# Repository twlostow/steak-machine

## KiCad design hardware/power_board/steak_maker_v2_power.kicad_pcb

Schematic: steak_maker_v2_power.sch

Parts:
B1, B2, B3, B4: NON-PLATED_HOLE3.0; MTG300; Part Number NON-PLATED_HOLE3.0
C1: CAER_470UF_10V_20%_500-1050X1150_LESR0R015; CAPPR500-1050X1150; Voltage 10V; Tolerance ±20%; Part Number CAER_470UF_10V_20%_500-1050X1150_LESR0R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
C2, C4: CCR_100NF_50V_10%_KEMET_C322C104K5R5TA; CAPRR508-318X508X660; Voltage 50VDC; Tolerance ±10%; Part Number CCR_100NF_50V_10%_KEMET_C322C104K5R5TA
C3: CAER_100UF_16V_20%_CHEMI-CON_APSA160ELL101MFA5G; CAPPR250-680X1080; Voltage 16V; Tolerance ±20%; Part Number CAER_100UF_16V_20%_CHEMI-CON_APSA160ELL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
D1, D2, D3, D4: 1N4007; DO-41; Voltage 1000V; Part Number 1N4007
IC1: LM7805CT_h; TO-220-H; Part Number LM7805CT_h
IC2, IC3: MOC3041M; DIP6-300
J1, J2, J4, J5, J9, J10, J11, J12: TYCO_62409-1; Part Number TYCO_62409-1
J8: MAIN
Q1, Q2: BT138-800; TO-220-v
R1, R2, R3, R4: RMF_150R_1%_0.125W_100PPM_1016-360X210; RES1016-360X210; Voltage ~~; Tolerance ±1%; Part Number RMF_150R_1%_0.125W_100PPM_1016-360X210
T1: Transformer_1P_1S; XFMR_BLOCK_10_1_6

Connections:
+5V: C3.1, C4.1, IC1.3, J8.1
/AC_L: J4.1, J9.1, J11.1, T1.1
/AC_N: J5.1, Q1.2 (A2), Q2.2 (A2), R3.2, R4.2, T1.2
/TRIAC1: J8.2, R1.1
/TRIAC2: J8.4, R2.1
GND: C1.2, C2.2, C3.2, C4.2, D3.2, D4.2, IC1.2, IC1.4, IC2.2, IC3.2, J1.1, J2.1, J8.3
unnamed: C1.1, C2.1, D1.1, D2.1, IC1.1
unnamed: D1.2, D3.1, T1.4
unnamed: D2.2, D4.1, T1.3
unnamed: IC2.1, R1.2
unnamed: IC2.4, Q1.3 (G)
unnamed: IC2.6, R3.1
unnamed: IC3.1, R2.2
unnamed: IC3.4, Q2.3 (G)
unnamed: IC3.6, R4.1
unnamed: J10.1, Q1.1 (A1)
unnamed: J12.1, Q2.1 (A1)

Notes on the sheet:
AC Input
Heater 1
Heater 2

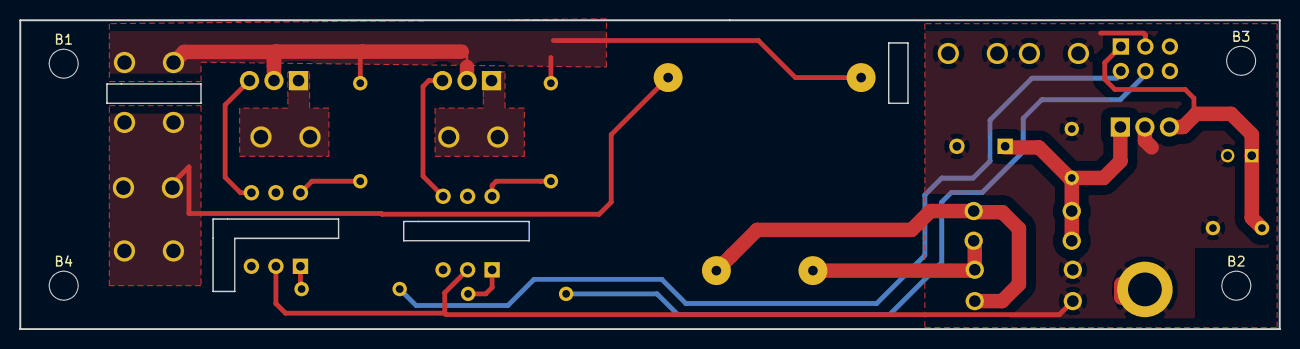
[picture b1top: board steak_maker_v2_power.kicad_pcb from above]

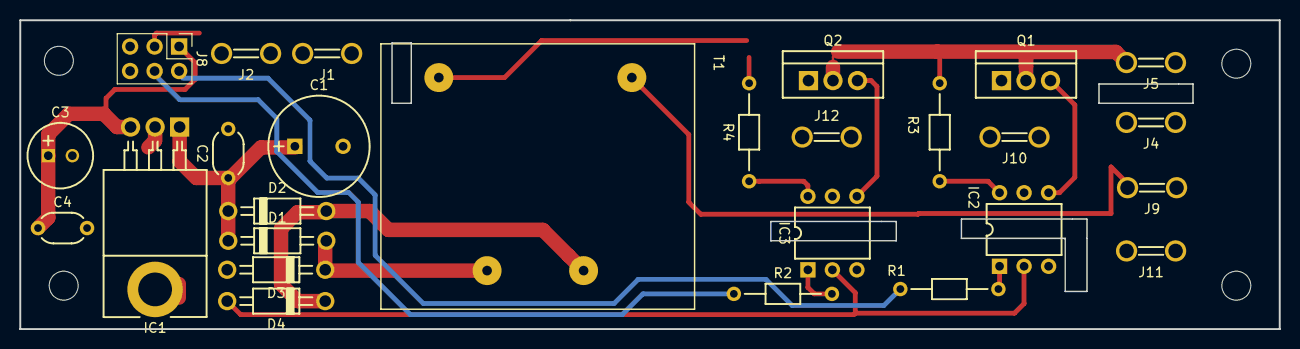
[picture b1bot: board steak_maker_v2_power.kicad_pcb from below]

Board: 2 copper layers, 130.5 x 32.0 mm, 31 parts (27 on the bottom side), 17 nets.

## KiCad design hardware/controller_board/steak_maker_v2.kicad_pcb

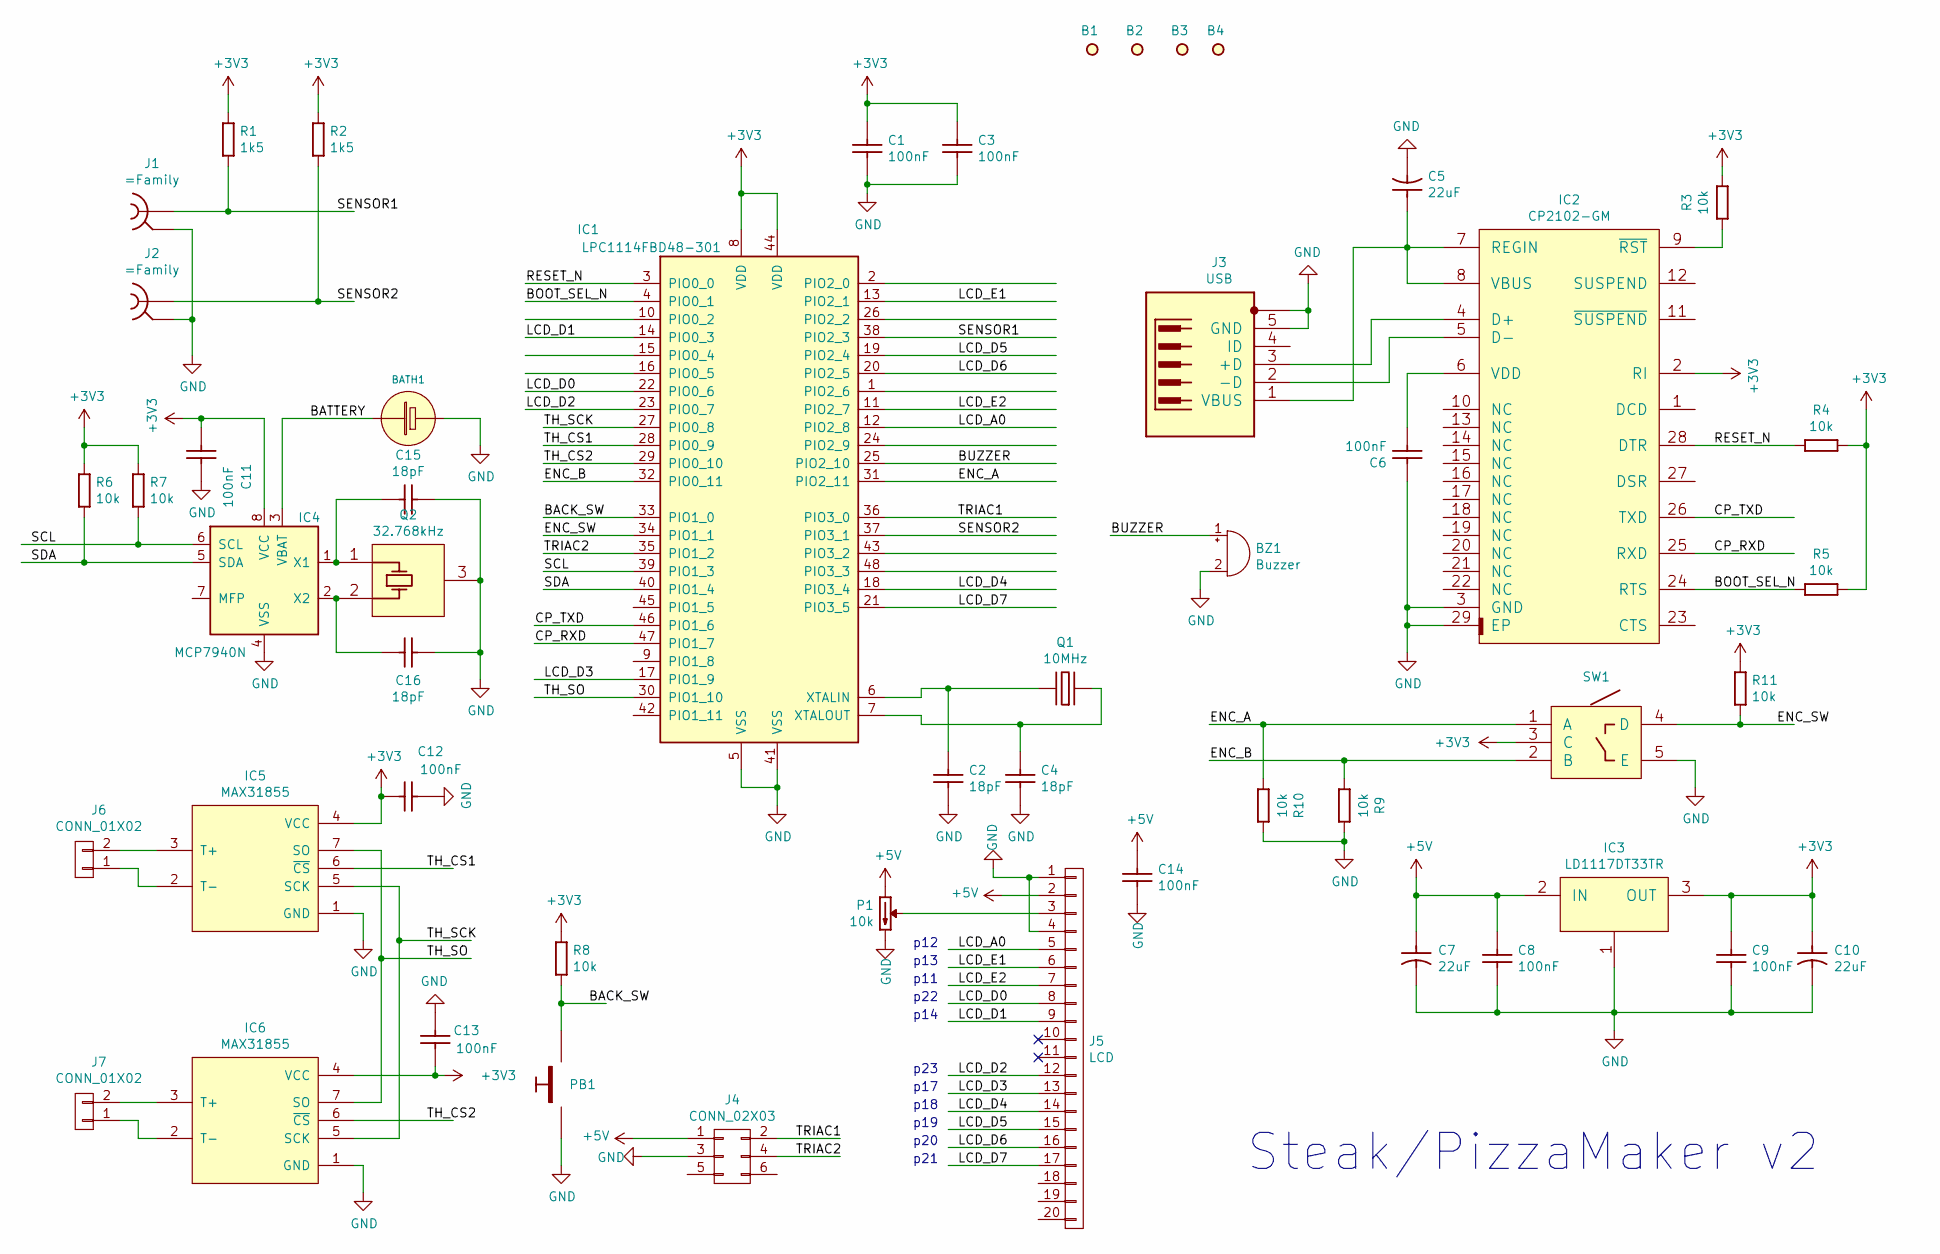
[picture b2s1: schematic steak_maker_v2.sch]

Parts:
B1, B2, B3, B4: PLATED_HOLE3.0_PAD6.0; MTG300_600; Part Number PLATED_HOLE3.0_PAD6.0
BATH1: BATH_KEYSTONE_103; Part Number BATH_KEYSTONE_103
BZ1: Buzzer; MagneticBuzzer_ProSignal_ABT-410-RC
C1, C3, C6, C8, C9, C11, C12, C13, C14: CC0603_100NF_100V_10%_X7R; CAPC1608X90N; Voltage 100V; Tolerance ±10%; Part Number CC0603_100NF_100V_10%_X7R
C2, C4, C15, C16: CC0603_18PF_50V_5%_NP0; CAPC1608X87N; Voltage 50V; Tolerance ±5%; Part Number CC0603_18PF_50V_5%_NP0
C5, C7, C10: CTE3528-21_22UF_10V_10%_LESR0700; CAPMP3528X210N; Voltage 10V; Tolerance ±10%; Part Number CTE3528-21_22UF_10V_10%_LESR0700
IC1: LPC1114FBD48-301; LQFP-48_7x7mm_Pitch0.5mm
IC2: CP2102-GM; QFN50P500X500X100-29N-S335; Part Number CP2102-GM
IC3: LD1117DT33TR; TO228P972X240-3N-R540X510; Part Number LD1117DT33TR
IC4: MCP7940N; SOIC127P600X175-8N
IC5, IC6: MAX31855; SOIC127P600X175-8N
J1, J2: LEMO_EPA.00.250.NTN; Part Number LEMO_EPA.00.250.NTN
J3: MOLEX_500075-1517; Part Number MOLEX_500075-1517
J4: CONN_02X03; COMATEL_389.0358.1.06.400
J5: LCD; COMATEL_385.0334.1.20.400
J6, J7: CONN_01X02; TerminalBlock_Pheonix_PT-3.5mm_2pol
P1: TRIM_12T_10K_BOURNS_3266W-1-103LF; TRIM_BOURNS_3266W; Tolerance ±10%; Part Number TRIM_12T_10K_BOURNS_3266W-1-103LF
PB1: PB_MULTIMEC_3ETL9-11.0; Part Number PB_MULTIMEC_3ETL9-11.0
Q1: XTAL_10MHZ_IQD_LFXTAL003166; XTAL1160X490X430; Part Number XTAL_10MHZ_IQD_LFXTAL003166
Q2: XTAL_32.768_KHZ_MICRO-CRYSTAL_MS3V-T1R; XTAL_MICRO-CRYSTAL_MS3V-T1R; Part Number XTAL_32.768_KHZ_MICRO-CRYSTAL_MS3V-T1R
R1, R2: R0603_1K5_1%_0.1W_100PPM; RESC1608X55N; Voltage ~~; Tolerance ±1%; Part Number R0603_1K5_1%_0.1W_100PPM
R3, R4, R5, R6, R7, R8, R9, R10, R11: R0603_10K_1%_0.1W_100PPM; RESC1608X55N; Voltage ~~; Tolerance ±1%; Part Number R0603_10K_1%_0.1W_100PPM
SW1: SW_ALPS_EC11B15242AE; SW_ALPS_EC11E; Part Number SW_ALPS_EC11B15242AE

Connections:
+3V3: C1.1, C3.1, C9.1, C10.1, C11.2, C12.2, C13.1, IC1.8 (VDD), IC1.44 (VDD), IC2.2 (RI), IC3.3 (OUT), IC4.8 (VCC), IC5.4 (VCC), IC6.4 (VCC), R1.1, R2.1, R3.2, R4.2, R5.2, R6.1, R7.1, R8.1, R11.1, SW1.3 (C)
+5V: C7.1, C8.1, C14.1, IC3.2 (IN), J4.1, J5.2, P1.1 (CCW)
/BACK_SW: IC1.33 (PIO1_0), PB1.3, PB1.4, R8.2
/BATTERY: BATH1.1 (PLUS), IC4.3 (VBAT)
/BOOT_SEL_N: IC1.4 (PIO0_1), IC2.24 (RTS), R5.1
/BUZZER: BZ1.1 (-), IC1.25 (PIO2_10)
/CP_RXD: IC1.47 (PIO1_7), IC2.25 (RXD)
/CP_TXD: IC1.46 (PIO1_6), IC2.26 (TXD)
/ENC_A: IC1.31 (PIO2_11), R10.2, SW1.1 (A)
/ENC_B: IC1.32 (PIO0_11), R9.2, SW1.2 (B)
/ENC_SW: IC1.34 (PIO1_1), R11.2, SW1.4 (D)
/LCD_A0: IC1.12 (PIO2_8), J5.5
/LCD_D0: IC1.22 (PIO0_6), J5.8
/LCD_D1: IC1.14 (PIO0_3), J5.9
/LCD_D2: IC1.23 (PIO0_7), J5.12
/LCD_D3: IC1.17 (PIO1_9), J5.13
/LCD_D4: IC1.18 (PIO3_4), J5.14
/LCD_D5: IC1.19 (PIO2_4), J5.15
/LCD_D6: IC1.20 (PIO2_5), J5.16
/LCD_D7: IC1.21 (PIO3_5), J5.17
/LCD_E1: IC1.13 (PIO2_1), J5.6
/LCD_E2: IC1.11 (PIO2_7), J5.7
/RESET_N: IC1.3 (PIO0_0), IC2.28 (DTR), R4.1
/SCL: IC1.39 (PIO1_3), IC4.6 (SCL), R7.2
/SDA: IC1.40 (PIO1_4), IC4.5 (SDA), R6.2
/SENSOR1: IC1.38 (PIO2_3), J1.1, R1.2
/SENSOR2: IC1.37 (PIO3_1), J2.1, R2.2
/TH_CS1: IC1.28 (PIO0_9), IC5.6 (~CS)
/TH_CS2: IC1.29 (PIO0_10), IC6.6 (~CS)
/TH_SCK: IC1.27 (PIO0_8), IC5.5 (SCK), IC6.5 (SCK)
/TH_SO: IC1.30 (PIO1_10), IC5.7 (SO), IC6.7 (SO)
/TRIAC1: IC1.36 (PIO3_0), J4.2
/TRIAC2: IC1.35 (PIO1_2), J4.4
GND: BATH1.2 (MINUS), BZ1.2 (+), C1.2, C2.2, C3.2, C4.2, C5.2, C6.1, C7.2, C8.2, C9.2, C10.2, C11.1, C12.1, C13.2, C14.2, C15.1, C16.1, IC1.5 (VSS), IC1.41 (VSS), IC2.3 (GND), IC2.29 (EP), IC3.1 (GND), IC4.4 (VSS), IC5.1 (GND), IC6.1 (GND), J1.2, J2.2, J3.5 (GND), J3.6 (SH), J4.3, J5.1, J5.4, P1.3 (CW), PB1.1, PB1.2, Q2.3 (GND), R9.1, R10.1, SW1.5 (E)
unnamed: C2.1, IC1.6 (XTALIN), Q1.1 (OSC1)
unnamed: C4.1, IC1.7 (XTALOUT), Q1.2 (OSC2)
unnamed: C5.1, IC2.7 (REGIN), IC2.8 (VBUS), J3.1 (VBUS)
unnamed: C6.2, IC2.6 (VDD)
unnamed: C15.2, IC4.1 (X1), Q2.1 (X)
unnamed: C16.2, IC4.2 (X2), Q2.2 (X)
unnamed: IC2.4 (D+), J3.3 (+D)
unnamed: IC2.5 (D-), J3.2 (-D)
unnamed: IC2.9 (~RST), R3.1
unnamed: IC5.2 (T-), J6.1
unnamed: IC5.3 (T+), J6.2
unnamed: IC6.2 (T-), J7.1
unnamed: IC6.3 (T+), J7.2
unnamed: J5.3, P1.2 (W)

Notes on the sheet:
Steak/PizzaMaker v2
p12
p13
p11
p22
p14
p23
p21
p20
p19
p18
p17

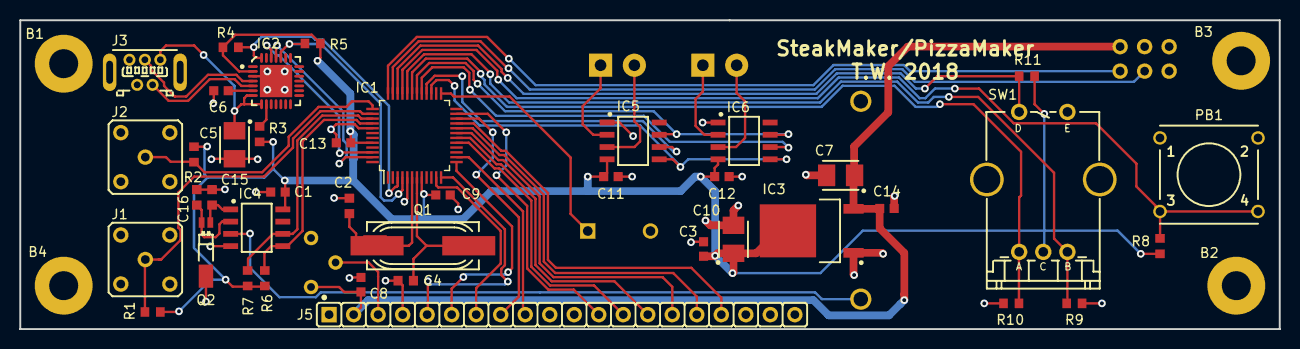
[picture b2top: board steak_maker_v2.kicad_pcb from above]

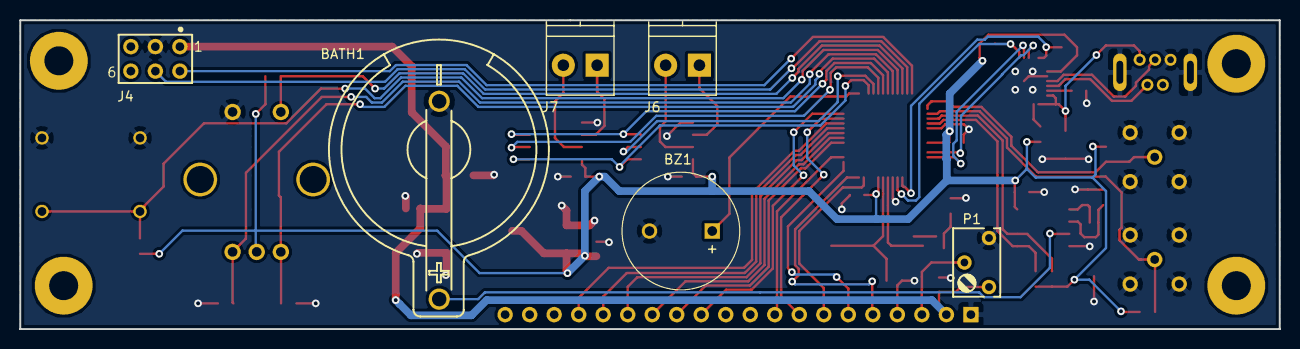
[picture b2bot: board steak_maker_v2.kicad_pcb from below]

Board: 2 copper layers, 130.5 x 32.0 mm, 51 parts (6 on the bottom side), 48 nets.

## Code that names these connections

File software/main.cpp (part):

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#include "rotary_encoder.h"
#include "spi_master.h"

LPCPin enc_a(2, 11, GPIOPin::INPUT);
LPCPin enc_b(0, 11, GPIOPin::INPUT);
LPCPin lcd_a0(2, 8, GPIOPin::OUTPUT);
LPCPin lcd_e1(2, 1, GPIOPin::OUTPUT);
LPCPin lcd_e2(2, 7, GPIOPin::OUTPUT);
LPCPin lcd_d0(0, 6, GPIOPin::OUTPUT); // pin 28
LPCPin lcd_d1(0, 3, GPIOPin::OUTPUT); // pin 27
LPCPin lcd_d2(0, 7, GPIOPin::OUTPUT); // pin 25
LPCPin lcd_d3(1, 9, GPIOPin::OUTPUT); // pin 26
LPCPin lcd_d4(3, 4, GPIOPin::OUTPUT);
LPCPin lcd_d5(2, 4, GPIOPin::OUTPUT);
LPCPin lcd_d6(2, 5, GPIOPin::OUTPUT);
LPCPin lcd_d7(3, 5, GPIOPin::OUTPUT);
LPCPin spi_sck(0, 8, GPIOPin::OUTPUT);
LPCPin spi_data(1, 10, GPIOPin::OUTPUT);
LPCPin spi_cs1(0, 9, GPIOPin::OUTPUT);
LPCPin spi_cs2(0, 10, GPIOPin::OUTPUT);
RotaryEncoder enc(&enc_a, &enc_b);
GPIOPin *lcd_data[] = {&lcd_d0, &lcd_d1, &lcd_d2, &lcd_d3, &lcd_d4, &lcd_d5, &lcd_d6, &lcd_d7};
LPCPin sw_enter(1, 1, GPIOPin::INPUT);
LPCPin sw_back(1, 0, GPIOPin::INPUT);
LPCPin pin_onewire1(2, 3, GPIOPin::OUTPUT);
LPCPin pin_onewire2(3, 1, GPIOPin::OUTPUT);
LPCPin pin_triac1(3, 0, GPIOPin::OUTPUT);
LPCPin pin_triac2(1, 2, GPIOPin::OUTPUT);

CERNTrashLCD *lcd;
Surface *screen;
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			pwm_cnt++;

		if (pwm_cnt <= pwm_setpoint)
			pin_triac1.Output(true);
		else
			pin_triac1.Output(false);

		cnt++;
	}
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
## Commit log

2013-01-09 initial version
2013-01-15 work in progress, temperature readout OK
2014-03-23 somewhat working version
2018-12-05 moved software sources to separate folder
2018-12-05 hardware: initial commit
2018-12-05 software: latest version, wip, dirty as hell

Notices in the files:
parts and their libraries:
This work is licensed under the Creative Commons CC-BY-SA 4.0 License. To the extent that circuit schematics that use Licensed Material can be considered to be ‘Adapted Material’, then the copyright holder waives article 3.b of the license with respect to these schematics.
